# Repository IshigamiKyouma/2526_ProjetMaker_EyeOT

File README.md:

# 2526_ProjetMaker_EyeOT

Projet de MANSARD Johann réalisé dans le cadre de l'option Maker.\
Lien de la vidéo: https://youtube.com/shorts/I4skJVQ_Xr0?feature=share
Lien du répo avec les exos: https://github.com/IshigamiKyouma/2526_Maker_Exercises

## 1. Description du Projet et rétroplanning
### 1.1. Contexte et objectifs

En tant que joueur passionné de League of Legends et "Main Vel'Koz", j'ai toujours été fasciné par le concept de ce champion :
une entité du Néant qui déconstruit la réalité pour accumuler des connaissances.

<details>
  <summary>Cliquez ici pour voir le modèle 3D de Vel'Koz</summary>
  <br>
  <div align="center">
    
    <p><i>Rendu 3D du modèle Vel'Koz (Source : Riot Games)</i></p>
  </div>
</details>

L'idée de ce projet est née d'une envie simple: briser le quatrième mur. Je ne voulais plus que Vel'Koz soit uniquement une image sur mon écran, mais qu'il devienne un compagnon physique capable de réagir, en temps réel, à l'intensité de mes parties.

L'objectif est de créer une figurine interactive qui agit comme une extension sensorielle du jeu. Grâce à l'intégration de l'API de Riot Games et de composants électroniques, la figurine "vit" au rythme de la faille:

* Réaction aux événements: Un feedback visuel lors de l'application des stacks de passif (LEDs hautes qui s'allument une à une) puis la centrale lors de l'activation du passif "Organic Deconstruction".

* Analyse des mouvements: Les tentacules se déplacent en fonction de la vitesse de déplacement en jeu

### 1.2. Solutions techniques

* **Cœur du système :** Microcontrôleur **STM32**, choisi pour sa gestion fluide des interruptions et ses multiples canaux PWM nécessaires au pilotage synchrone des servomoteurs et du bus NeoPixel.
* **Communication de données :** Script en **Python** interrogeant la *Live Client Data API* de Riot Games à haute fréquence (HTTPS) et transmettant les états à la STM via une liaison **Série (USB)**.
* **Actionneurs & Visuels :**  3 Servomoteurs pour l'animation cinétique.
    * 3 LEDs adressables (NeoPixel) pour les stacks et 1 bloc circulaire pour l'œil central.
* **Gestion de l'énergie :** Conception d'un **PCB dédié** à la distribution de puissance, incluant un filtrage par condensateurs pour lisser les appels de courant des servos et une alimentation externe **5V 3A**.
* **Structure & Design :** Modélisation CAO et impression 3D. Le châssis est conçu pour masquer l'électronique dans le socle.

---

### 1.3. Obtention des valeurs

Pour obtenir:
* la vitesse de déplacement du joueur: on utilisera directement l'API
* les stacks de passif: Apparaissent visuelement quand on clique sur un ennemie

### Mécanisme de mouvement : Le système à câbles
Pour reproduire le mouvement fluide et "invertébré" des tentacules de Vel'Koz avec seulement 3 servomoteurs, le projet utilise un système de **flexion par câbles (tendeurs)** :

* **Principe :** Chaque tentacule est imprimée en matériau semi-rigide ou composée de vertèbres articulées.
* **Transmission :** Un câble (type fil de pêche ou nylon) parcourt l'intérieur de la tentacule jusqu'à l'extrémité. 
* **Actionnement :** Le servomoteur, situé dans la base, tire sur le câble pour courber la structure. Un ressort interne ou la mémoire de forme du plastique permet le retour à la position initiale.
* **Résultat :** Cela permet d'obtenir une ondulation organique plutôt qu'une rotation robotique rigide.

---

### Rétro-planning

| Session | Phase | Objectif principal |
| ------- | ----- | ------------------ |
| **TP 1** | **PoC Logiciel** | Script Python : récupération des données API et envoi vers l'ESP32. |
| **TP 2** | **Électronique** | Montage breadboard : test simultané des 3 servos et des LEDs. |
| **TP 3** | **Design PCB** | Routage du circuit d'alimentation et préparation à la soudure. |
| **TP 4** | **Modélisation 3D** | CAO du corps et du mécanisme de tension des tentacules. |
| **TP 5** | **Mécanique** | Assemblage des servos et tests des câbles de traction. |
| **TP 6** | **Intégration** | Soudure finale sur PCB et insertion dans la structure 3D. |
| **TP 7** | **Calibration** | Mapping des data LoL -> angles de servos et finitions visuelles. |

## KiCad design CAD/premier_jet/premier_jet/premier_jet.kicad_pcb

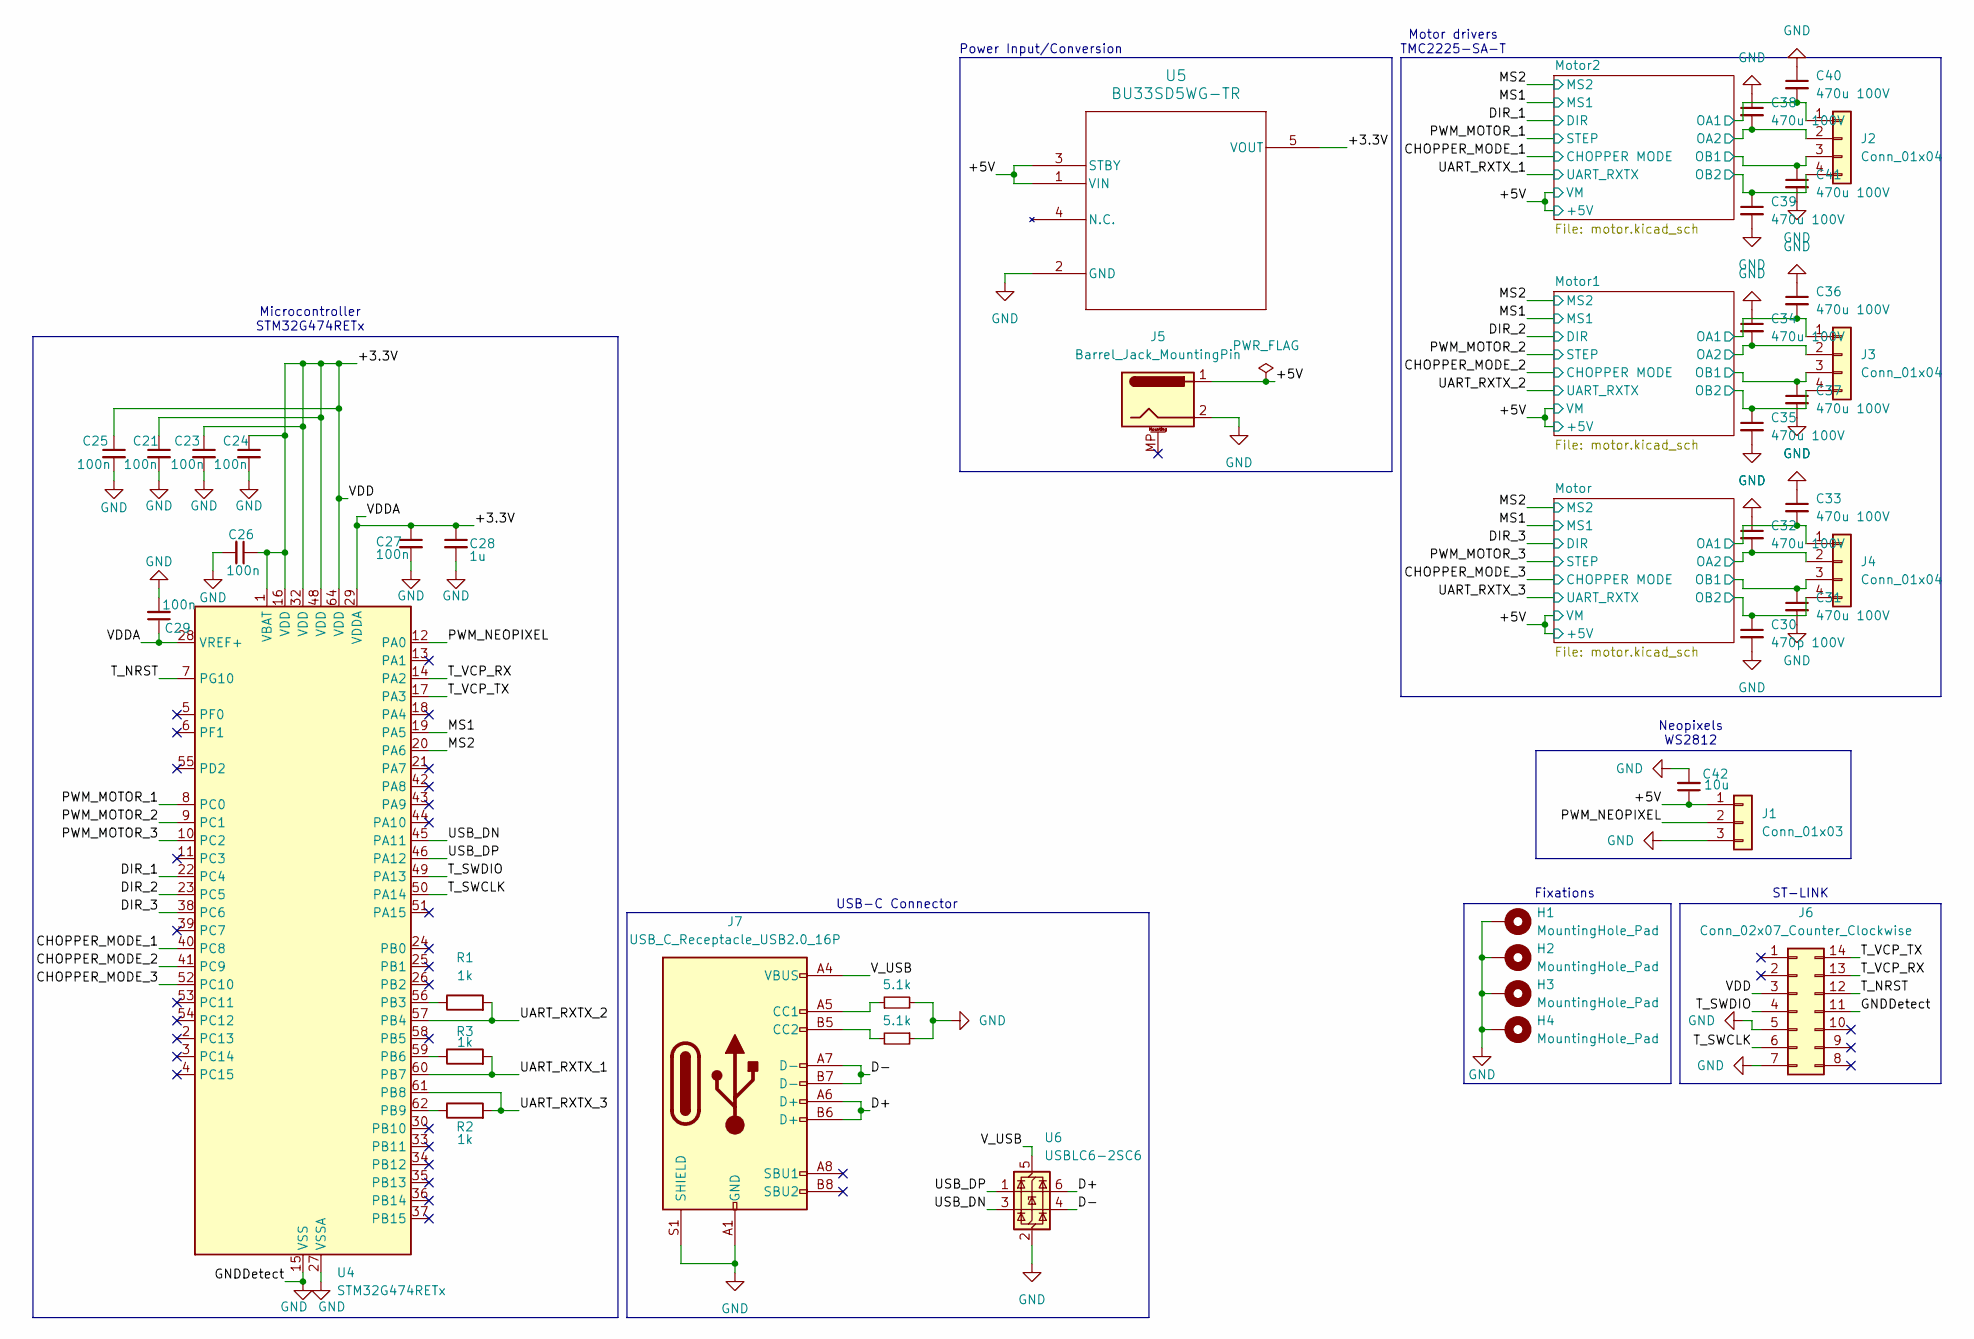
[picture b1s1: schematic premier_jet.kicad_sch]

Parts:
C21, C23, C24, C25, C26, C27, C29: 100n; C_0402_1005Metric
C28: 1u; C_0402_1005Metric
C30: 470p 100V; C_0603_1608Metric
C31, C32, C33, C34, C35, C36, C37, C38, C39, C40, C41: 470u 100V; C_0603_1608Metric
C42: 10u; C_0603_1608Metric
H1, H2, H3, H4: MountingHole_Pad; MountingHole_3.2mm_M3_Pad
J1: Conn_01x03; JST_PH_B3B-PH-K_1x03_P2.00mm_Vertical
J2, J3, J4: Conn_01x04; JST_PH_B4B-PH-K_1x04_P2.00mm_Vertical
J5: Barrel_Jack_MountingPin; BarrelJack_Wuerth_694106106102_2.0x5.5mm
J6: Conn_02x07_Counter_Clockwise; PinHeader_2x07_P2.54mm_Vertical_SMD
J7: USB_C_Receptacle_USB2.0_16P; USB_C_Receptacle_GCT_USB4105-xx-A_16P_TopMnt_Horizontal
R1, R2, R3: 1k; R_0402_1005Metric
R4, R5: 5.1k; R_0805_2012Metric
U4: STM32G474RETx; LQFP-64_10x10mm_P0.5mm
U5: BU33SD5WG-TR; SSOP5_ROM
U6: USBLC6-2SC6; SOT-23-6

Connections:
/+3.3V: C21.1, C23.1, C24.1, C25.1, C26.1, C27.1, C28.1, C29.1, J6.3, U4.1 (VBAT), U4.16 (VDD), U4.28 (VREF+), U4.29 (VDDA), U4.32 (VDD), U4.48 (VDD), U4.64 (VDD), U5.5 (VOUT)
/+5V: C42.1, J1.1, J5.1, U5.1 (VIN), U5.3 (STBY); also elsewhere on the board
/CHOPPER_MODE_1: U4.40 (PC8); also elsewhere on the board
/CHOPPER_MODE_2: U4.41 (PC9); also elsewhere on the board
/CHOPPER_MODE_3: U4.52 (PC10); also elsewhere on the board
/D+: J7.A6 (D+), J7.B6 (D+), U6.6 (I/O1)
/D-: J7.A7 (D-), J7.B7 (D-), U6.4 (I/O2)
/DIR_1: U4.22 (PC4); also elsewhere on the board
/DIR_2: U4.23 (PC5); also elsewhere on the board
/DIR_3: U4.38 (PC6); also elsewhere on the board
/MS1: U4.19 (PA5); also elsewhere on the board
/MS2: U4.20 (PA6); also elsewhere on the board
/Motor1/OA1: C36.2, J3.1; also elsewhere on the board
/Motor1/OA2: C34.2, J3.2; also elsewhere on the board
/Motor1/OB1: C37.1, J3.3; also elsewhere on the board
/Motor1/OB2: C35.1, J3.4; also elsewhere on the board
/Motor2/OA1: C40.2, J2.1; also elsewhere on the board
/Motor2/OA2: C38.2, J2.2; also elsewhere on the board
/Motor2/OB1: C41.1, J2.3; also elsewhere on the board
/Motor2/OB2: C39.1, J2.4; also elsewhere on the board
/Motor/OA1: C33.2, J4.1; also elsewhere on the board
/Motor/OA2: C32.2, J4.2; also elsewhere on the board
/Motor/OB1: C31.1, J4.3; also elsewhere on the board
/Motor/OB2: C30.1, J4.4; also elsewhere on the board
/PWM_MOTOR_1: U4.8 (PC0); also elsewhere on the board
/PWM_MOTOR_2: U4.9 (PC1); also elsewhere on the board
/PWM_MOTOR_3: U4.10 (PC2); also elsewhere on the board
/PWM_NEOPIXEL: J1.2, U4.12 (PA0)
/T_NRST: J6.12, U4.7 (PG10)
/T_SWCLK: J6.6, U4.50 (PA14)
/T_SWDIO: J6.4, U4.49 (PA13)
/T_VCP_RX: J6.13, U4.14 (PA2)
/T_VCP_TX: J6.14, U4.17 (PA3)
/UART_RXTX_1: R3.2, U4.60 (PB7); also elsewhere on the board
/UART_RXTX_2: R1.2, U4.57 (PB4); also elsewhere on the board
/UART_RXTX_3: R2.2, U4.61 (PB8); also elsewhere on the board
/USB_DN: U4.45 (PA11), U6.3 (I/O2)
/USB_DP: U4.46 (PA12), U6.1 (I/O1)
/V_USB: J7.A4 (VBUS), J7.A9 (VBUS), J7.B4 (VBUS), J7.B9 (VBUS), U6.5 (VBUS)
GND: C21.2, C23.2, C24.2, C25.2, C26.2, C27.2, C28.2, C29.2, C30.2, C31.2, C32.1, C33.1, C34.1, C35.2, C36.1, C37.2, C38.1, C39.2, C40.1, C41.2, C42.2, H1.1, H2.1, H3.1, H4.1, J1.3, J5.2, J6.5, J6.7, J6.11, J7.A1 (GND), J7.A12 (GND), J7.B1 (GND), J7.B12 (GND), J7.S1 (SHIELD), R4.2, R5.1, U4.15 (VSS), U4.27 (VSSA), U4.31 (VSS), U4.47 (VSS), U4.63 (VSS), U5.2 (GND), U6.2 (GND); also elsewhere on the board
unnamed: J7.A5 (CC1), R4.1
unnamed: J7.B5 (CC2), R5.2
unnamed: R1.1, U4.56 (PB3)
unnamed: R3.1, U4.59 (PB6)
unnamed: R2.1, U4.62 (PB9)

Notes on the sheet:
Motor drivers TMC2225-SA-T
Microcontroller STM32G474RETx
Neopixels WS2812
Power Input/Conversion
USB-C Connector
Fixations
ST-LINK

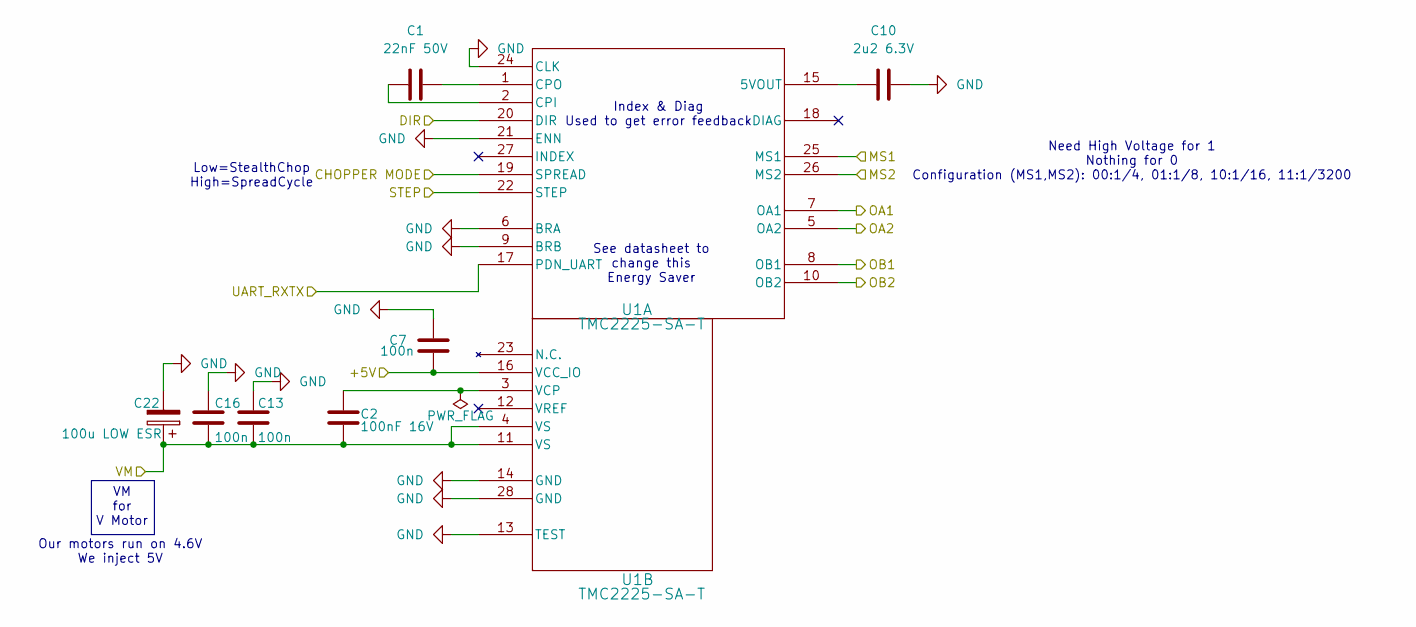
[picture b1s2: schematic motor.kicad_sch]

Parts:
C1: 22nF 50V; C_0603_1608Metric
C2: 100nF 16V; C_0402_1005Metric
C7, C13, C16: 100n; C_0402_1005Metric
C10: 2u2 6.3V; C_0402_1005Metric
C22: 100u LOW ESR; CP_Elec_6.3x5.4
U1: TMC2225-SA-T; HTSSOP28_TMC2225_TRI

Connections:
/+5V: C2.2, C7.2, C13.2, C16.2, C22.1, U1.4 (VS), U1.11 (VS), U1.16 (VCC_IO); also elsewhere on the board
/CHOPPER_MODE_3: U1.19 (SPREAD); also elsewhere on the board
/DIR_3: U1.20 (DIR); also elsewhere on the board
/MS1: U1.25 (MS1); also elsewhere on the board
/MS2: U1.26 (MS2); also elsewhere on the board
/Motor/OA1: U1.7 (OA1); also elsewhere on the board
/Motor/OA2: U1.5 (OA2); also elsewhere on the board
/Motor/OB1: U1.8 (OB1); also elsewhere on the board
/Motor/OB2: U1.10 (OB2); also elsewhere on the board
/PWM_MOTOR_3: U1.22 (STEP); also elsewhere on the board
/UART_RXTX_3: U1.17 (PDN_UART); also elsewhere on the board
GND: C7.1, C10.2, C13.1, C16.1, C22.2, U1.6 (BRA), U1.9 (BRB), U1.13 (TEST), U1.14 (GND), U1.21 (ENN), U1.24 (CLK), U1.28 (GND); also elsewhere on the board
unnamed: C10.1, U1.15 (5VOUT)
unnamed: C1.1, U1.2 (CPI)
unnamed: C1.2, U1.1 (CPO)
unnamed: C2.1, U1.3 (VCP)

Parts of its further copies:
C3, C12: 100u LOW ESR; CP_Elec_6.3x5.4
C4, C5, C9, C14, C15, C19: 100n; C_0402_1005Metric
C6, C17: 100nF 16V; C_0402_1005Metric
C8, C18: 22nF 50V; C_0603_1608Metric
C11, C20: 2u2 6.3V; C_0402_1005Metric
U2, U3: TMC2225-SA-T; HTSSOP28_TMC2225_TRI

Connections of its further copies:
/+5V: C3.1, C4.2, C5.2, C6.2, C9.2, C12.1, C14.2, C15.2, C17.2, C19.2, U2.4 (VS), U2.11 (VS), U2.16 (VCC_IO), U3.4 (VS), U3.11 (VS), U3.16 (VCC_IO); also elsewhere on the board
/CHOPPER_MODE_1: U3.19 (SPREAD); also elsewhere on the board
/CHOPPER_MODE_2: U2.19 (SPREAD); also elsewhere on the board
/DIR_1: U3.20 (DIR); also elsewhere on the board
/DIR_2: U2.20 (DIR); also elsewhere on the board
/MS1: U2.25 (MS1), U3.25 (MS1); also elsewhere on the board
/MS2: U2.26 (MS2), U3.26 (MS2); also elsewhere on the board
/Motor1/OA1: U2.7 (OA1); also elsewhere on the board
/Motor1/OA2: U2.5 (OA2); also elsewhere on the board
/Motor1/OB1: U2.8 (OB1); also elsewhere on the board
/Motor1/OB2: U2.10 (OB2); also elsewhere on the board
/Motor2/OA1: U3.7 (OA1); also elsewhere on the board
/Motor2/OA2: U3.5 (OA2); also elsewhere on the board
/Motor2/OB1: U3.8 (OB1); also elsewhere on the board
/Motor2/OB2: U3.10 (OB2); also elsewhere on the board
/PWM_MOTOR_1: U3.22 (STEP); also elsewhere on the board
/PWM_MOTOR_2: U2.22 (STEP); also elsewhere on the board
/UART_RXTX_1: U3.17 (PDN_UART); also elsewhere on the board
/UART_RXTX_2: U2.17 (PDN_UART); also elsewhere on the board
GND: C3.2, C4.1, C5.1, C9.1, C11.2, C12.2, C14.1, C15.1, C19.1, C20.2, U2.6 (BRA), U2.9 (BRB), U2.13 (TEST), U2.14 (GND), U2.21 (ENN), U2.24 (CLK), U2.28 (GND), U3.6 (BRA), U3.9 (BRB), U3.13 (TEST), U3.14 (GND), U3.21 (ENN), U3.24 (CLK), U3.28 (GND); also elsewhere on the board
unnamed: C11.1, U2.15 (5VOUT)
unnamed: C8.1, U2.2 (CPI)
unnamed: C8.2, U2.1 (CPO)
unnamed: C6.1, U2.3 (VCP)
unnamed: C20.1, U3.15 (5VOUT)
unnamed: C18.1, U3.2 (CPI)
unnamed: C18.2, U3.1 (CPO)
unnamed: C17.1, U3.3 (VCP)

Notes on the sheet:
VM for V Motor
Low=StealthChop High=SpreadCycle
See datasheet to change this Energy Saver
Our motors run on 4.6V We inject 5V
Index & Diag Used to get error feedback
Need High Voltage for 1 Nothing for 0 Configuration (MS1,MS2): 00:1/4, 01:1/8, 10:1/16, 11:1/3200

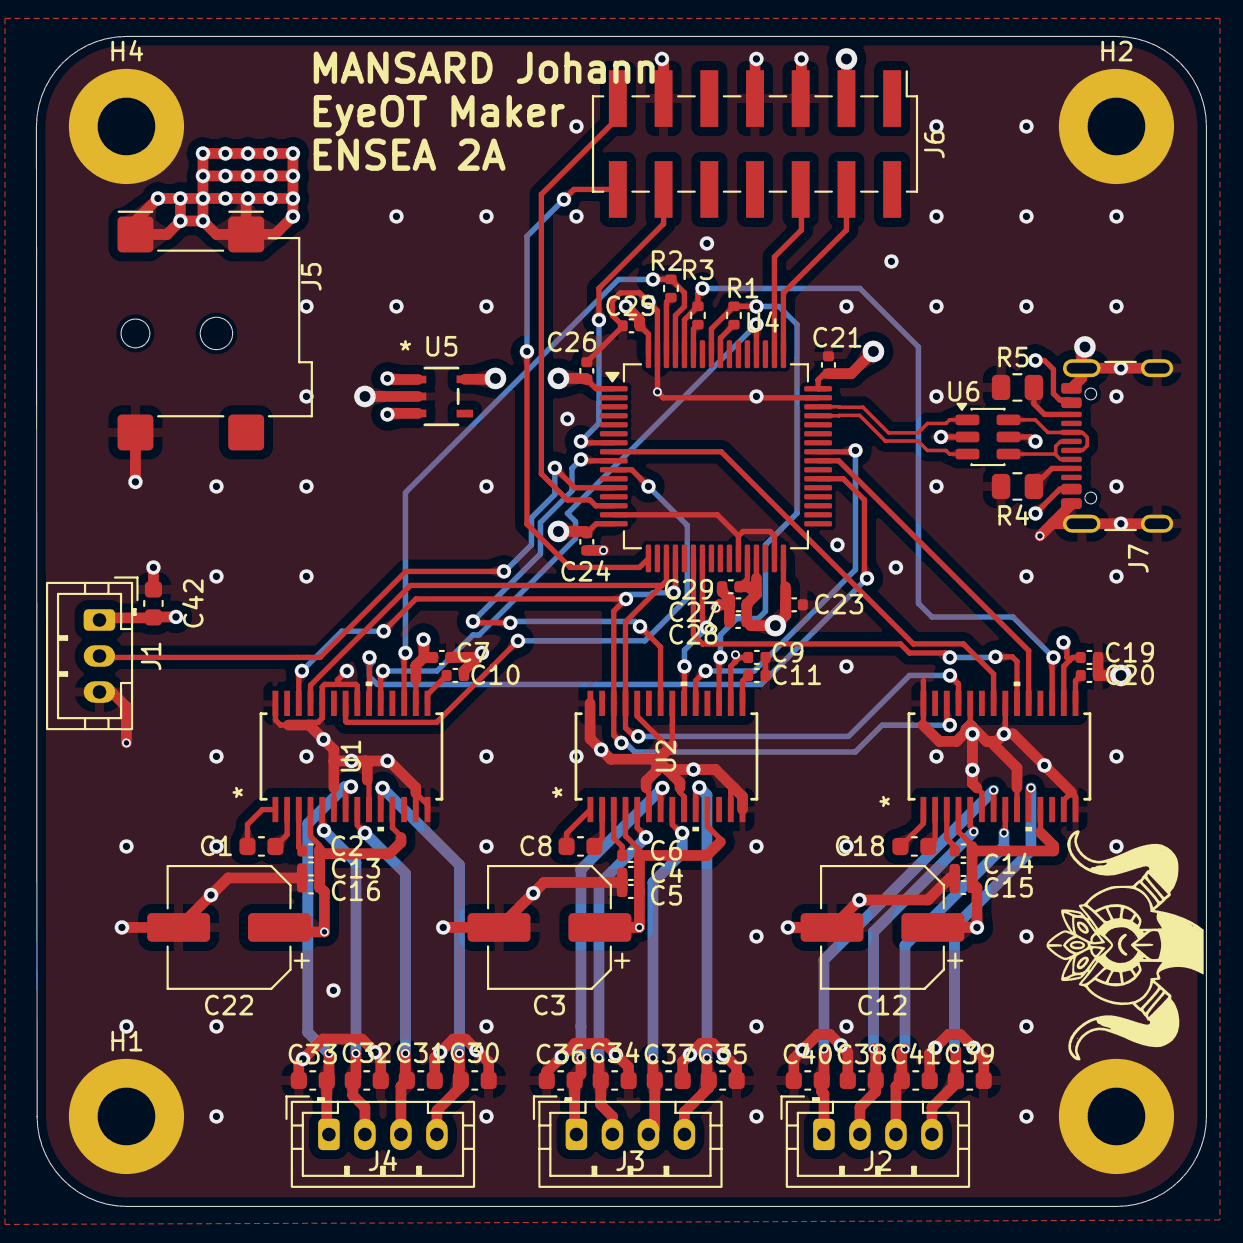
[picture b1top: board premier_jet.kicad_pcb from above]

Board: 4 copper layers, 65.0 x 65.0 mm, 64 parts (0 on the bottom side), 57 nets.

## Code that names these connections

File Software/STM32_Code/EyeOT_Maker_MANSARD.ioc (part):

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Mcu.Name=STM32G474R(B-C-E)Tx
Mcu.Package=LQFP64
Mcu.UserName=STM32G474RETx
PA0.Signal=S_TIM2_CH1
PA11.Mode=Device
PA11.Signal=USB_DM
PA12.Mode=Device
PA12.Signal=USB_DP
PA13.Signal=SYS_JTMS-SWDIO
PA14.Signal=SYS_JTCK-SWCLK
PA5.Signal=GPIO_Output
PA6.Signal=GPIO_Output
PB3.Signal=USART2_TX
PB4.Signal=USART2_RX
PB6.Signal=USART1_TX
PB7.Signal=USART1_RX
PB8-BOOT0.Signal=USART3_RX
PB9.Signal=USART3_TX
PC0.Signal=S_TIM1_CH1
PC1.Signal=S_TIM1_CH2
PC10.Signal=GPIO_Output
PC2.Signal=S_TIM1_CH3
PC4.Signal=GPIO_Output
PC5.Signal=GPIO_Output
PC6.Signal=GPIO_Output
PC8.Signal=GPIO_Output
PC9.Signal=GPIO_Output
RCC.HSE_VALUE=8000000
RCC.SYSCLKFreq_VALUE=16000000
board=custom

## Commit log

2026-01-18 Update Markdown Readme
2026-02-12 Add Suivi.txt
2026-02-16 :Readme update
2026-02-18 :CAD added
2026-02-18 :Hardware added
2026-02-18 Fix formatting of Step-Down Alim entry
2026-02-18 removed ussb-uart bridge
2026-02-19 Updated KiCad
2026-03-08 Update pcb
2026-04-07 Long overdue update
